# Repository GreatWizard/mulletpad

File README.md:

# mulletpad

A 17-key numpad with USB Type-C

Keyboard Maintainer: coseyfannitutti (https://github.com/coseyfannitutti)

Hardware Supported: mulletpad, atmega32u4  
Hardware Availability: https://github.com/coseyfannitutti

Make example for this keyboard (after setting up your build environment):

    make coseyfannitutti:mullet:default

See the [build environment setup](https://docs.qmk.fm/#/getting_started_build_tools) and the [make instructions](https://docs.qmk.fm/#/getting_started_make_guide) for more information. Brand new to QMK? Start with our [Complete Newbs Guide](https://docs.qmk.fm/#/newbs).

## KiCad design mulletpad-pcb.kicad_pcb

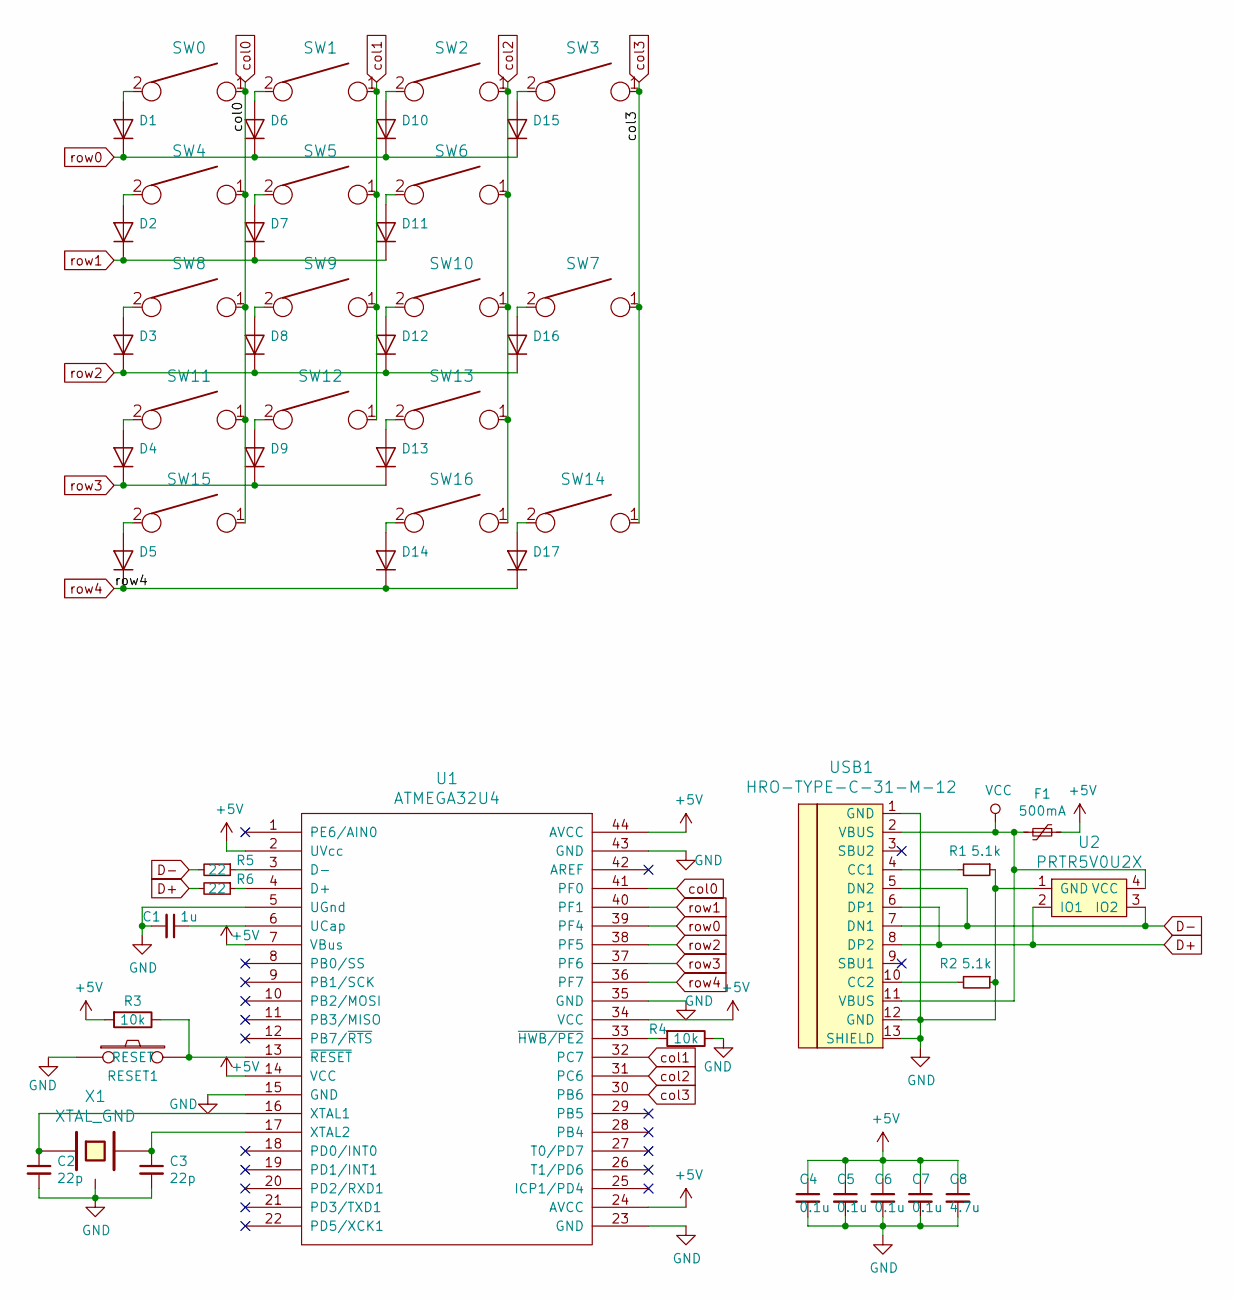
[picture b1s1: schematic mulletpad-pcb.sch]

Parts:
C1: 1u; C_0603_1608Metric
C2, C3: 22p; C_0603_1608Metric
C4, C5, C6, C7: 0.1u; C_0603_1608Metric
C8: 4.7u; C_0603_1608Metric
D1, D2, D3, D4, D5, D6, D7, D8, D9, D10, D11, D12, D13, D14, D15, D16, D17: D_SOD-123
F1: 500mA; R_0805_2012Metric
R1, R2: 5.1k; R_0603_1608Metric
R3, R4: 10k; R_0603_1608Metric
R5, R6: 22; R_0603_1608Metric
RESET1: RESET; SW_SPST_TL3342
SW0, SW1, SW2, SW3, SW4, SW5, SW6, SW8, SW9, SW10, SW11, SW12, SW13, SW16: KEYSW; SW_Cherry_MX1A_1.00u_PCB-NOSCREEN
SW7, SW14: KEYSW; SW_Cherry_MX1A_2.00u_Vertical_PCB
SW15: KEYSW; SW_Cherry_MX1A_2.00u_PCB_FLIPPED
U1: ATMEGA32U4; QFN-44-1EP_7x7mm_P0.5mm_EP5.2x5.2mm
U2: PRTR5V0U2X; SOT143B
USB1: HRO-TYPE-C-31-M-12; HRO-TYPE-C-31-M-12-HandSoldering
X1: XTAL_GND; FA-238

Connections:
+5V: C4.1, C5.1, C6.1, C7.1, C8.1, F1.1, R3.2, U1.2 (UVcc), U1.7 (VBus), U1.14 (VCC), U1.24 (AVCC), U1.34 (VCC), U1.44 (AVCC)
D+: R6.2, U2.2 (IO1), USB1.6 (DP1), USB1.8 (DP2)
D-: R5.2, U2.3 (IO2), USB1.5 (DN2), USB1.7 (DN1)
GND: C1.2, C2.2, C3.2, C4.2, C5.2, C6.2, C7.2, C8.2, R1.1, R2.1, R4.1, RESET1.1, U1.5 (UGnd), U1.15 (GND), U1.23 (GND), U1.35 (GND), U1.43 (GND), U2.1 (GND), USB1.1 (GND), USB1.12 (GND), USB1.13 (SHIELD), X1.3
unnamed: C1.1, U1.6 (UCap)
unnamed: C2.1, U1.16 (XTAL1), X1.1
unnamed: C3.1, U1.17 (XTAL2), X1.2
unnamed: D1.2 (A), SW0.2
unnamed: D2.2 (A), SW4.2
unnamed: D3.2 (A), SW8.2
unnamed: D4.2 (A), SW11.2
unnamed: D5.2 (A), SW15.2
unnamed: D6.2 (A), SW1.2
unnamed: D7.2 (A), SW5.2
unnamed: D8.2 (A), SW9.2
unnamed: D9.2 (A), SW12.2
unnamed: D10.2 (A), SW2.2
unnamed: D11.2 (A), SW6.2
unnamed: D12.2 (A), SW10.2
unnamed: D13.2 (A), SW13.2
unnamed: D14.2 (A), SW16.2
unnamed: D15.2 (A), SW3.2
unnamed: D16.2 (A), SW7.2
unnamed: D17.2 (A), SW14.2
unnamed: R1.2, USB1.4 (CC1)
unnamed: R2.2, USB1.10 (CC2)
unnamed: R3.1, RESET1.2, U1.13 (~RESET)
unnamed: R4.2, U1.33 (~HWB/PE2)
unnamed: R5.1, U1.3 (D-)
unnamed: R6.1, U1.4 (D+)
VCC: F1.2, U2.4 (VCC), USB1.2 (VBUS), USB1.11 (VBUS)
col0: SW0.1, SW4.1, SW8.1, SW11.1, SW15.1, U1.41 (PF0)
col1: SW1.1, SW5.1, SW9.1, SW12.1, U1.32 (PC7)
col2: SW2.1, SW6.1, SW10.1, SW13.1, SW16.1, U1.31 (PC6)
col3: SW3.1, SW7.1, SW14.1, U1.30 (PB6)
row0: D1.1 (K), D6.1 (K), D10.1 (K), D15.1 (K), U1.39 (PF4)
row1: D2.1 (K), D7.1 (K), D11.1 (K), U1.40 (PF1)
row2: D3.1 (K), D8.1 (K), D12.1 (K), D16.1 (K), U1.38 (PF5)
row3: D4.1 (K), D9.1 (K), D13.1 (K), U1.37 (PF6)
row4: D5.1 (K), D14.1 (K), D17.1 (K), U1.36 (PF7)

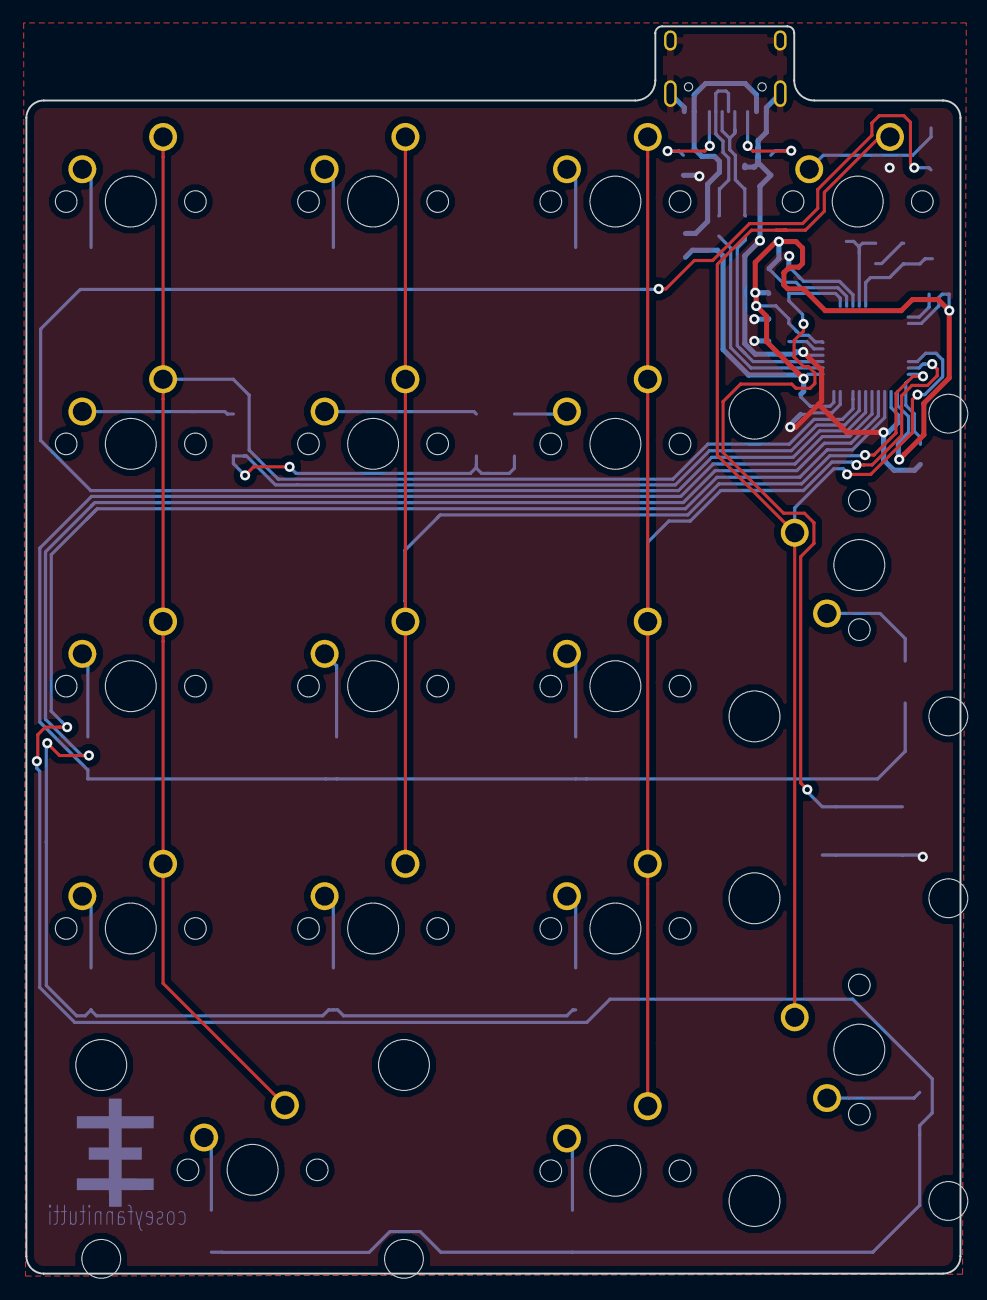
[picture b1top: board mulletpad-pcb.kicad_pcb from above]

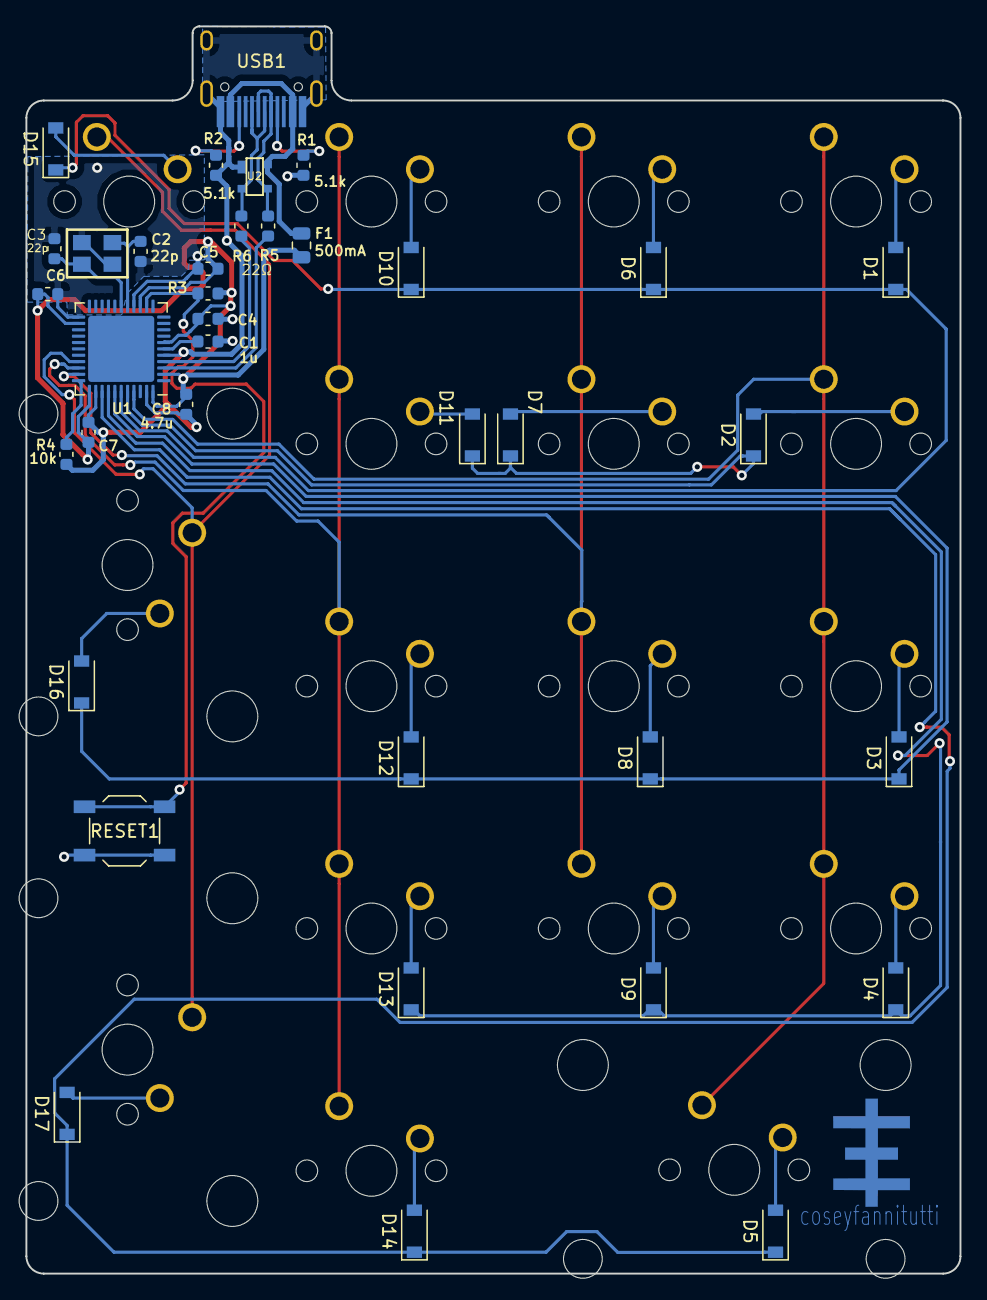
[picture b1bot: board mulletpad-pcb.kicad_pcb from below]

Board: 2 copper layers, 73.4 x 98.1 mm, 54 parts (37 on the bottom side), 40 nets.

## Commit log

2019-05-10 Create LICENSE
2019-05-10 added logo
2019-05-14 add gerber files
2019-05-16 update ground fills for usb port and xtal
2019-05-17 Update gnd fills for xtal
2019-05-21 update component labels
2019-05-21 remove switch outlines from screenprint
2019-06-19 add fillets to case middle layers
2019-06-19 clean up gnd fills
2019-06-20 remove backups
2019-06-26 clean up schematic
